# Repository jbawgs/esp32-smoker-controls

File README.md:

This is my esp32 smoker controller firmware and kicad drawings for the pcb.
It works, I used it all last summer, if you define "works" very loosely. I cooked the display and didn't care to replace it (and never finished its code) as I was perfectly fine using MQTT to control it, and also use that MQTT feed to populate a database for reporting purposes, which is not in the files here because I can't get into the ec2 instance it was hosted on atm ¯\_(ツ)_/¯ 
If a crazy person were to build this mess, i used an app on android called IOT MQTT Panel Pro to control everything remotely

Despite sucking at cpp, this thing was stable as a rock and held temps withing 3 degrees of target on my giant vertical smoker for days at a time, at least as soon as I realized I should move the tangle of ribbon cables away from the 120vac lines at the relay. As soon as it was usable I stopped development because I was tired boss, so its a mess. But maybe something of interest to see in there. My first swing at any hardware development as well as CPP, I was pretty proud at the time.
Anywhere you see the word "redacted" I pulled out a hard-coded password, key or SSID of some kind lmao

parts are a 30 pin ESP32, ads1115, 4 channel relay board, a 5v psu, capacitor for smoothing power into the ads board, assorted resistors for the voltage divider for temp probes, pt1000 temp probes, a crapload of headers, two miles of wires, a mini12864 3d printer display like this one:

https://www.amazon.com/gp/product/B09BKY5K84/ref=ppx_yo_dt_b_search_asin_title?ie=UTF8&psc=1

Combo rotary encoder! you can see how everything is wired up in the kicad schematic except for the display, I made a custom ribbon cable for that as the pin headers on that board are a wreck imo (not an expert) but you can see the pinouts here:

https://www.bjonnh.net/article/20221126_mini_12864/

Main control loop inspired by Dan Borello on his pismoker project, awesome

Libraries:

	https://github.com/me-no-dev/ESPAsyncWebServer.git
	ayushsharma82/AsyncElegantOTA@^2.2.7
	adafruit/Adafruit ADS1X15@^2.4.0
	olikraus/U8g2@^2.34.17
	adafruit/Adafruit SSD1306@^2.5.7
	adafruit/Adafruit GFX Library@^1.11.5
	https://github.com/igorantolic/ai-esp32-rotary-encoder
	https://github.com/ripred/Smooth/
	adafruit/SdFat - Adafruit Fork@^2.2.1
	br3ttb/PID@^1.2.1
	knolleary/PubSubClient@^2.8
	bblanchon/ArduinoJson@^6.21.2
	adafruit/Adafruit NeoPixel@^1.11.0

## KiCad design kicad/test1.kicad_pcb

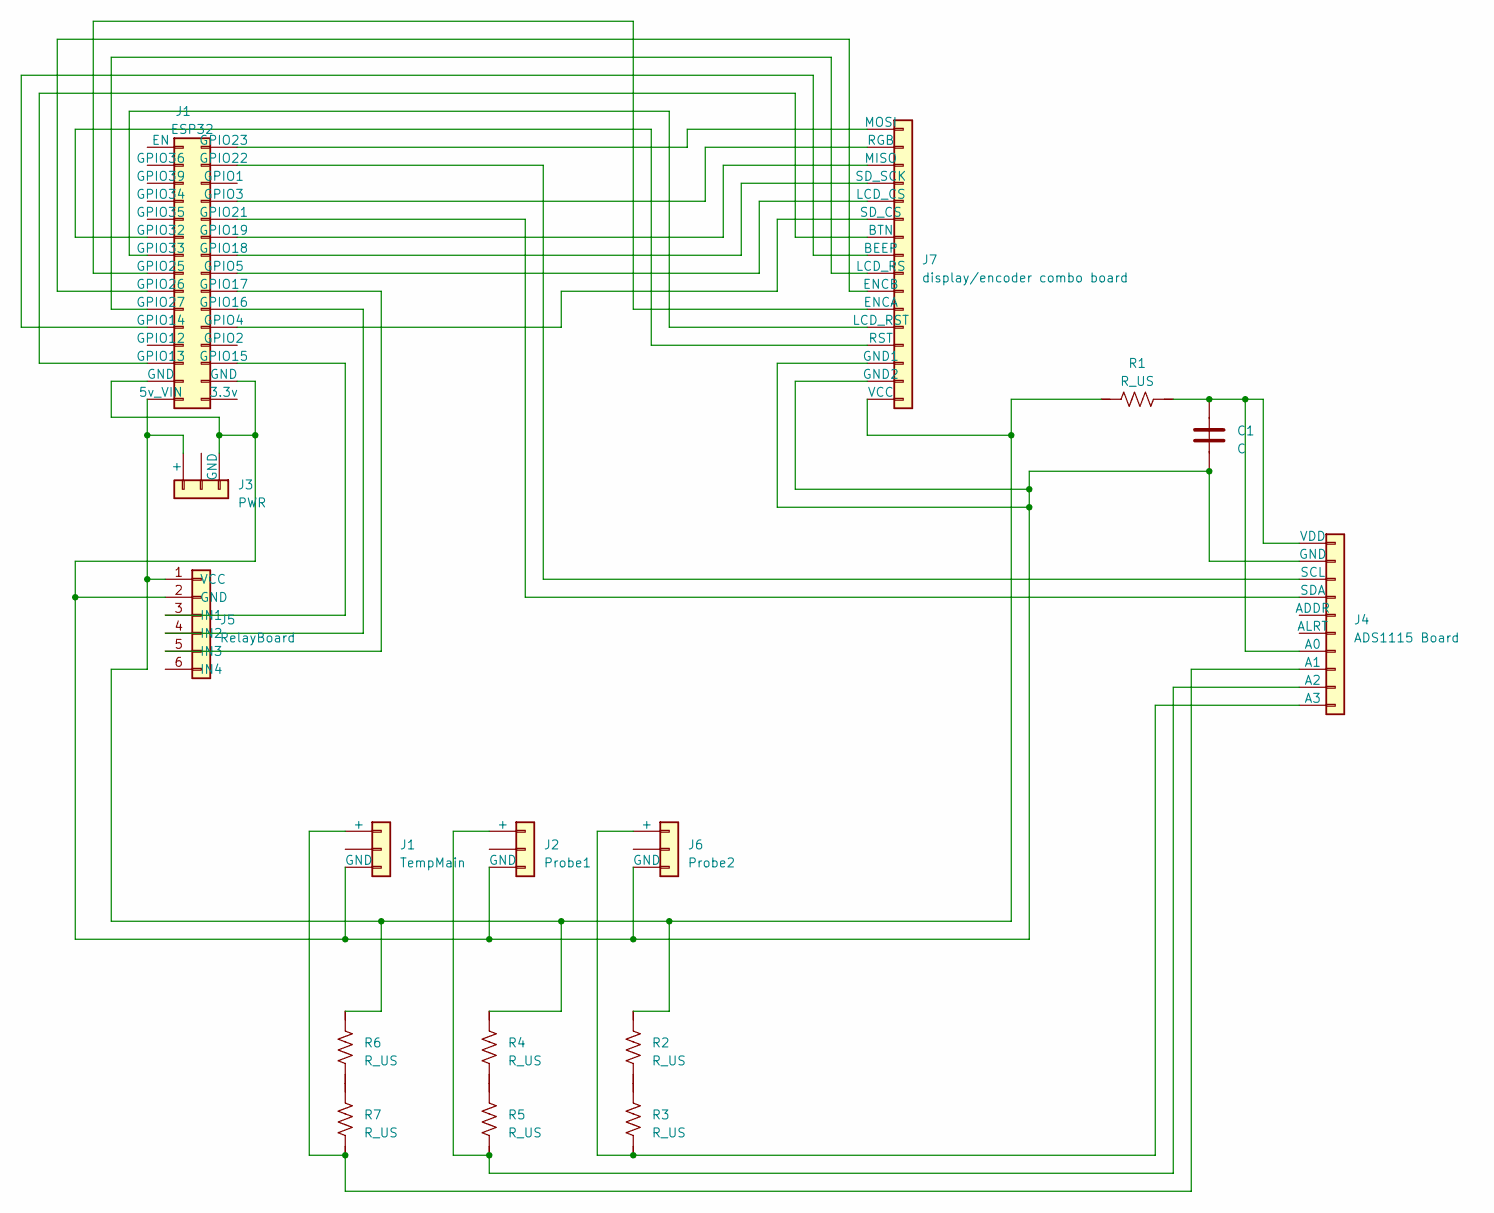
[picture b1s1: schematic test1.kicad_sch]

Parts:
C1: C; CP_Radial_D8.0mm_P3.50mm
ESP32: J1; ESP32 PinHeader_2x15_P2.54mm_Vertical
J1: TempMain; PinHeader_1x03_P2.54mm_Vertical
J2: Probe1; PinHeader_1x03_P2.54mm_Vertical
J3: PWR; PinHeader_1x03_P2.54mm_Vertical
J4: ADS1115 Board; PinHeader_1x10_P2.54mm_Vertical
J5: RelayBoard; PinHeader_1x06_P2.54mm_Vertical
J6: Probe2; PinHeader_1x03_P2.54mm_Vertical
J7: display/encoder combo board; PinHeader_1x16_P2.54mm_Vertical
R1, R2, R3, R4, R5, R6, R7: R_US; R_Axial_DIN0204_L3.6mm_D1.6mm_P2.54mm_Vertical

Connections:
unnamed: ESP32.63 (5v_VIN), J3.3 (+), J5.1 (VCC), J7.16 (VCC), R1.1, R2.2, R4.2, R6.2
unnamed: ESP32.3 (GPIO3), J7.2 (RGB)
unnamed: ESP32.4 (GPIO4), J7.6 (SD_CS)
unnamed: ESP32.5 (GPIO5), J7.5 (LCD_CS)
unnamed: ESP32.13 (GPIO13), J7.7 (BTN)
unnamed: ESP32.14 (GPIO14), J7.8 (BEEP)
unnamed: ESP32.15 (GPIO15), J5.3 (IN1)
unnamed: ESP32.16 (GPIO16), J5.4 (IN2)
unnamed: ESP32.17 (GPIO17), J5.5 (IN3)
unnamed: ESP32.18 (GPIO18), J7.4 (SD_SCK)
unnamed: ESP32.19 (GPIO19), J7.3 (MISO)
unnamed: ESP32.21 (GPIO21), J4.4 (SDA)
unnamed: ESP32.22 (GPIO22), J4.3 (SCL)
unnamed: ESP32.23 (GPIO23), J7.1 (MOSI)
unnamed: ESP32.25 (GPIO25), J7.11 (ENCA)
unnamed: ESP32.26 (GPIO26), J7.10 (ENCB)
unnamed: ESP32.27 (GPIO27), J7.9 (LCD_RS)
unnamed: ESP32.32 (GPIO32), J7.13 (RST)
unnamed: ESP32.33 (GPIO33), J7.12 (LCD_RST)
unnamed: J1.1 (+), J4.8 (A1), R7.1
unnamed: C1.2, ESP32.61 (GND), ESP32.62 (GND), J1.3 (GND), J2.3 (GND), J3.1 (GND), J4.2 (GND), J5.2 (GND), J6.3 (GND), J7.14 (GND1), J7.15 (GND2)
unnamed: J2.1 (+), J4.9 (A2), R5.1
unnamed: C1.1, J4.1 (VDD), J4.7 (A0), R1.2
unnamed: J4.10 (A3), J6.1 (+), R3.1
unnamed: R2.1, R3.2
unnamed: R4.1, R5.2
unnamed: R6.1, R7.2

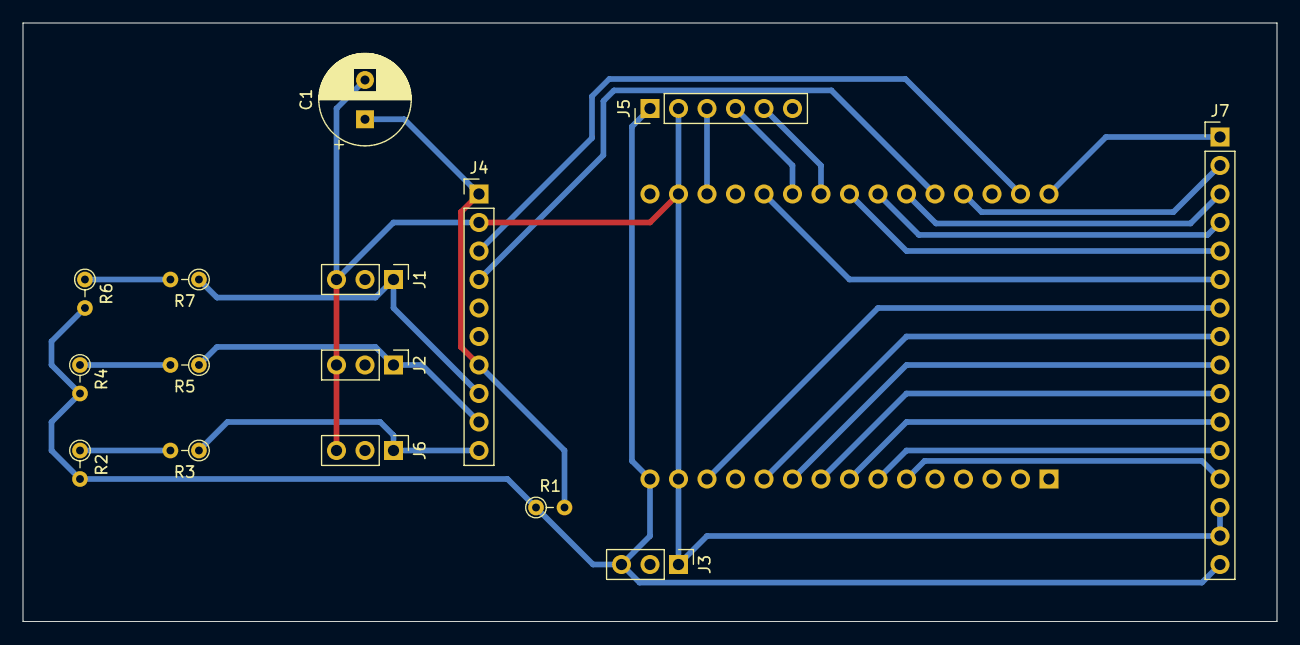
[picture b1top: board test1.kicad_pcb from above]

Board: 2 copper layers, 111.8 x 53.3 mm, 16 parts (1 on the bottom side), 27 nets.

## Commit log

2024-05-23 here
2024-05-23 kicad
